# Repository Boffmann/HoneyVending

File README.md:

# Honey Vending
`Honey Vending` is a vending machine for honey I am building. This repository contains all assets regarding software and hardware.

## Components
The honey vending machine consists of multiple components and a software program.

* Customers can insert money via a programmable coin acceptor like [this one](https://www.sparkfun.com/products/11636).
* The currently insterted amount is shown via a [TM1637 Display Module](https://www.amazon.com/DEVMO-Digital-Display-Module-Arduino/dp/B07R64BC38/ref=sr_1_1_sspa?keywords=tm1637&qid=1644671514&sr=8-1-spons&psc=1&spLa=ZW5jcnlwdGVkUXVhbGlmaWVyPUExVEc0TVhXVzVPQVNMJmVuY3J5cHRlZElkPUEwMDExODY5MjVIRVJISzI5SlFRTCZlbmNyeXB0ZWRBZElkPUEwMTgzMTM3M0JCWDJUNTJPTUNSJndpZGdldE5hbWU9c3BfYXRmJmFjdGlvbj1jbGlja1JlZGlyZWN0JmRvTm90TG9nQ2xpY2s9dHJ1ZQ==).
* All products are behind individually addressable doors that are controled by 12V electromagnetic locks like [this](https://www.amazon.com/uxcell-Electromagnetic-Solenoid-Assembly-Electirc/dp/B07TMWY94C/ref=sr_1_6?keywords=12v+door+lock&qid=1644671675&sr=8-6).
* Each door is linked to a button on a customly designed button rack.

The entire machine is managed by a ESP32 microcontroller that runs a custom program and links all parts.

## Structure
The project is structured as follows:

* **CADs**: Contains CAD files for all individual components and PCBs that are featured in this project
* **src**: The source files for the software programm controling the vending machines workflow

## Deploy
TODO

## Run tests
The unittests feature an independent build workflow using CMake. They cover all code that does not directly interact with the ESP hardware.

To compile and run unittests make sure to have `CMake` installed and perform following commands:

```
mkdir build && cd build
cmake ..
make
./unittest
```

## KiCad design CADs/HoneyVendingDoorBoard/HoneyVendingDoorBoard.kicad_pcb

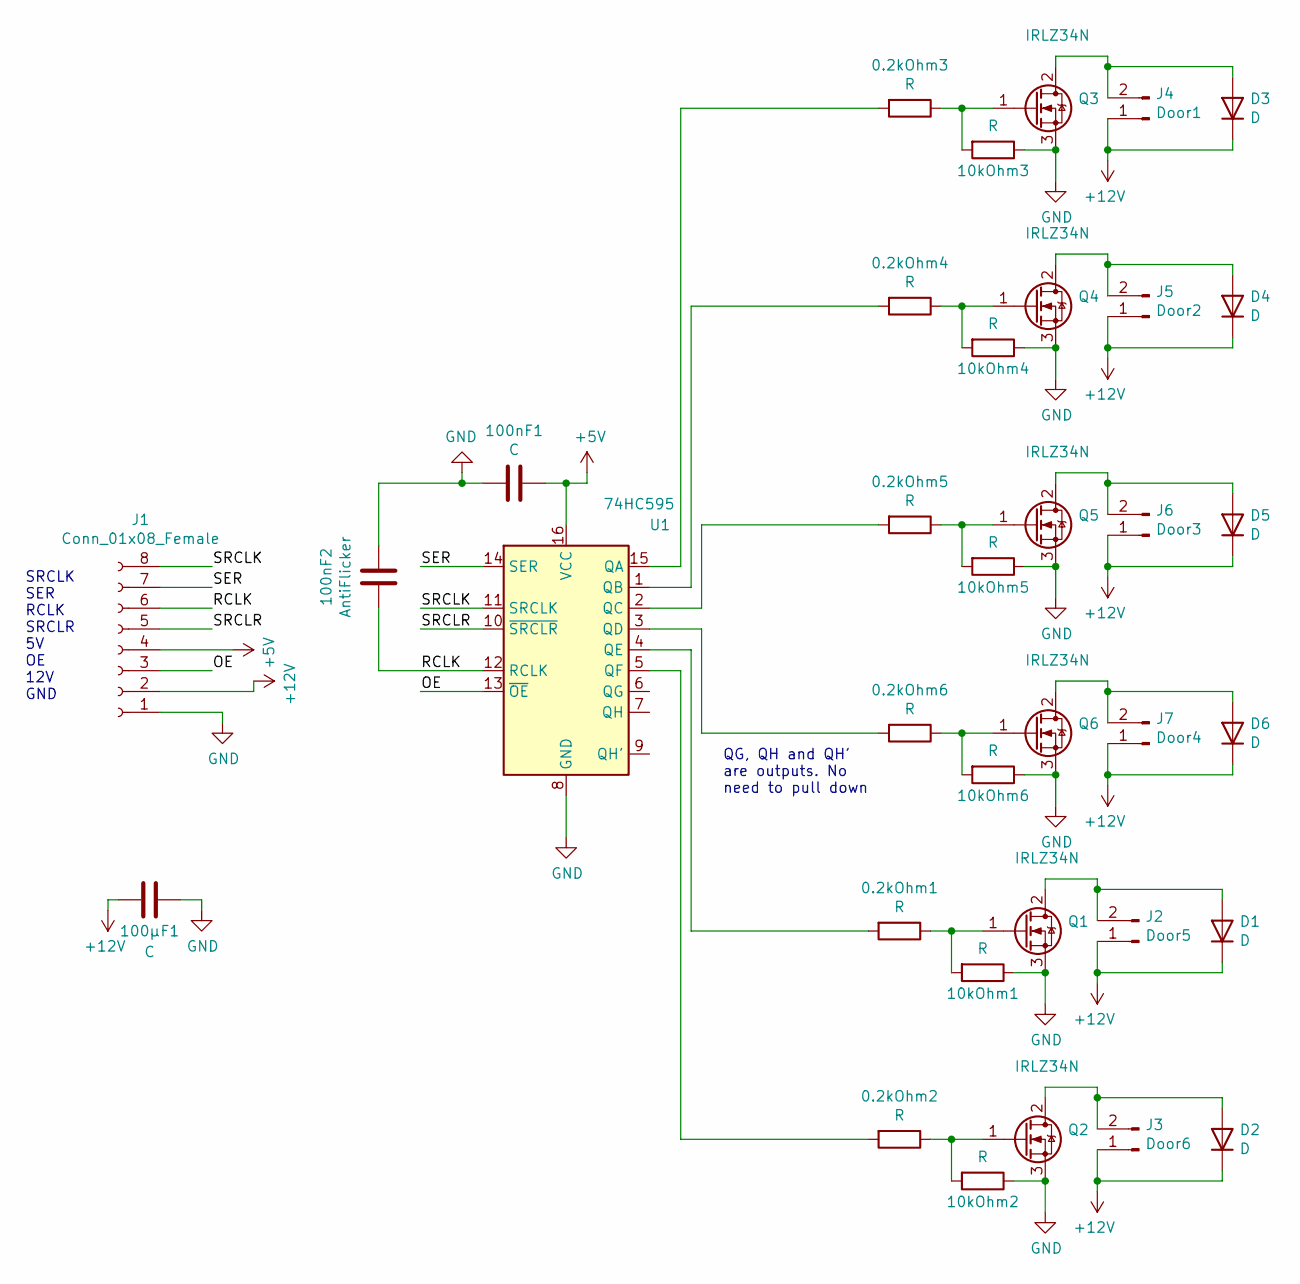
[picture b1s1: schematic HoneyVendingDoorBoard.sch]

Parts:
0.2kOhm1, 0.2kOhm2, 0.2kOhm3, 0.2kOhm4, 0.2kOhm5, 0.2kOhm6, 10kOhm1, 10kOhm2, 10kOhm3, 10kOhm4, 10kOhm5, 10kOhm6: R; R_0805_2012Metric_Pad1.15x1.40mm_HandSolder
100nF1: C; C_Disc_D6.0mm_W2.5mm_P5.00mm
100nF2: AntiFlicker; C_Disc_D6.0mm_W2.5mm_P5.00mm
100µF1: C; CP_Radial_D8.0mm_P3.50mm
D1, D2, D3, D4, D5, D6: D; D_DO-41_SOD81_P5.08mm_Vertical_AnodeUp
J1: Conn_01x08_Female; PinHeader_2x04_P2.54mm_Vertical
J2: Door5; PinHeader_1x02_P2.54mm_Vertical
J3: Door6; PinHeader_1x02_P2.54mm_Vertical
J4: Door1; PinHeader_1x02_P2.54mm_Vertical
J5: Door2; PinHeader_1x02_P2.54mm_Vertical
J6: Door3; PinHeader_1x02_P2.54mm_Vertical
J7: Door4; PinHeader_1x02_P2.54mm_Vertical
Q1, Q2, Q3, Q4, Q5, Q6: IRLZ34N; TO-220-3_Vertical
U1: 74HC595

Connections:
+5V: 100nF1.1, J1.4, U1.16 (VCC)
+12V: 100µF1.1, D1.1 (K), D2.1 (K), D3.1 (K), D4.1 (K), D5.1 (K), D6.1 (K), J1.2, J2.1, J3.1, J4.1, J5.1, J6.1, J7.1; also elsewhere on the board
/OE: J1.3, U1.13 (~OE)
/RCLK: 100nF2.2, J1.6, U1.12 (RCLK)
/SER: J1.7, U1.14 (SER)
/SRCLK: J1.8, U1.11 (SRCLK)
/SRCLR: J1.5, U1.10 (~SRCLR)
GND: 10kOhm1.1, 10kOhm2.1, 10kOhm3.1, 10kOhm4.1, 10kOhm5.1, 10kOhm6.1, 100nF1.2, 100nF2.1, 100µF1.2, J1.1, Q1.3 (S), Q2.3 (S), Q3.3 (S), Q4.3 (S), Q5.3 (S), Q6.3 (S), U1.8 (GND); also elsewhere on the board
unnamed: 0.2kOhm1.1, 10kOhm1.2, Q1.1 (G)
unnamed: 0.2kOhm1.2, U1.4 (QE)
unnamed: 0.2kOhm2.1, 10kOhm2.2, Q2.1 (G)
unnamed: 0.2kOhm2.2, U1.5 (QF)
unnamed: 0.2kOhm3.1, 10kOhm3.2, Q3.1 (G)
unnamed: 0.2kOhm3.2, U1.15 (QA)
unnamed: 0.2kOhm4.1, 10kOhm4.2, Q4.1 (G)
unnamed: 0.2kOhm4.2, U1.1 (QB)
unnamed: 0.2kOhm5.1, 10kOhm5.2, Q5.1 (G)
unnamed: 0.2kOhm5.2, U1.2 (QC)
unnamed: 0.2kOhm6.1, 10kOhm6.2, Q6.1 (G)
unnamed: 0.2kOhm6.2, U1.3 (QD)
unnamed: D1.2 (A), J2.2, Q1.2 (D)
unnamed: D2.2 (A), J3.2, Q2.2 (D)
unnamed: D3.2 (A), J4.2, Q3.2 (D)
unnamed: D4.2 (A), J5.2, Q4.2 (D)
unnamed: D5.2 (A), J6.2, Q5.2 (D)
unnamed: D6.2 (A), J7.2, Q6.2 (D)

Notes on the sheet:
SRCLK SER RCLK SRCLR 5V OE 12V GND
QG, QH and QH' are outputs. No need to pull down

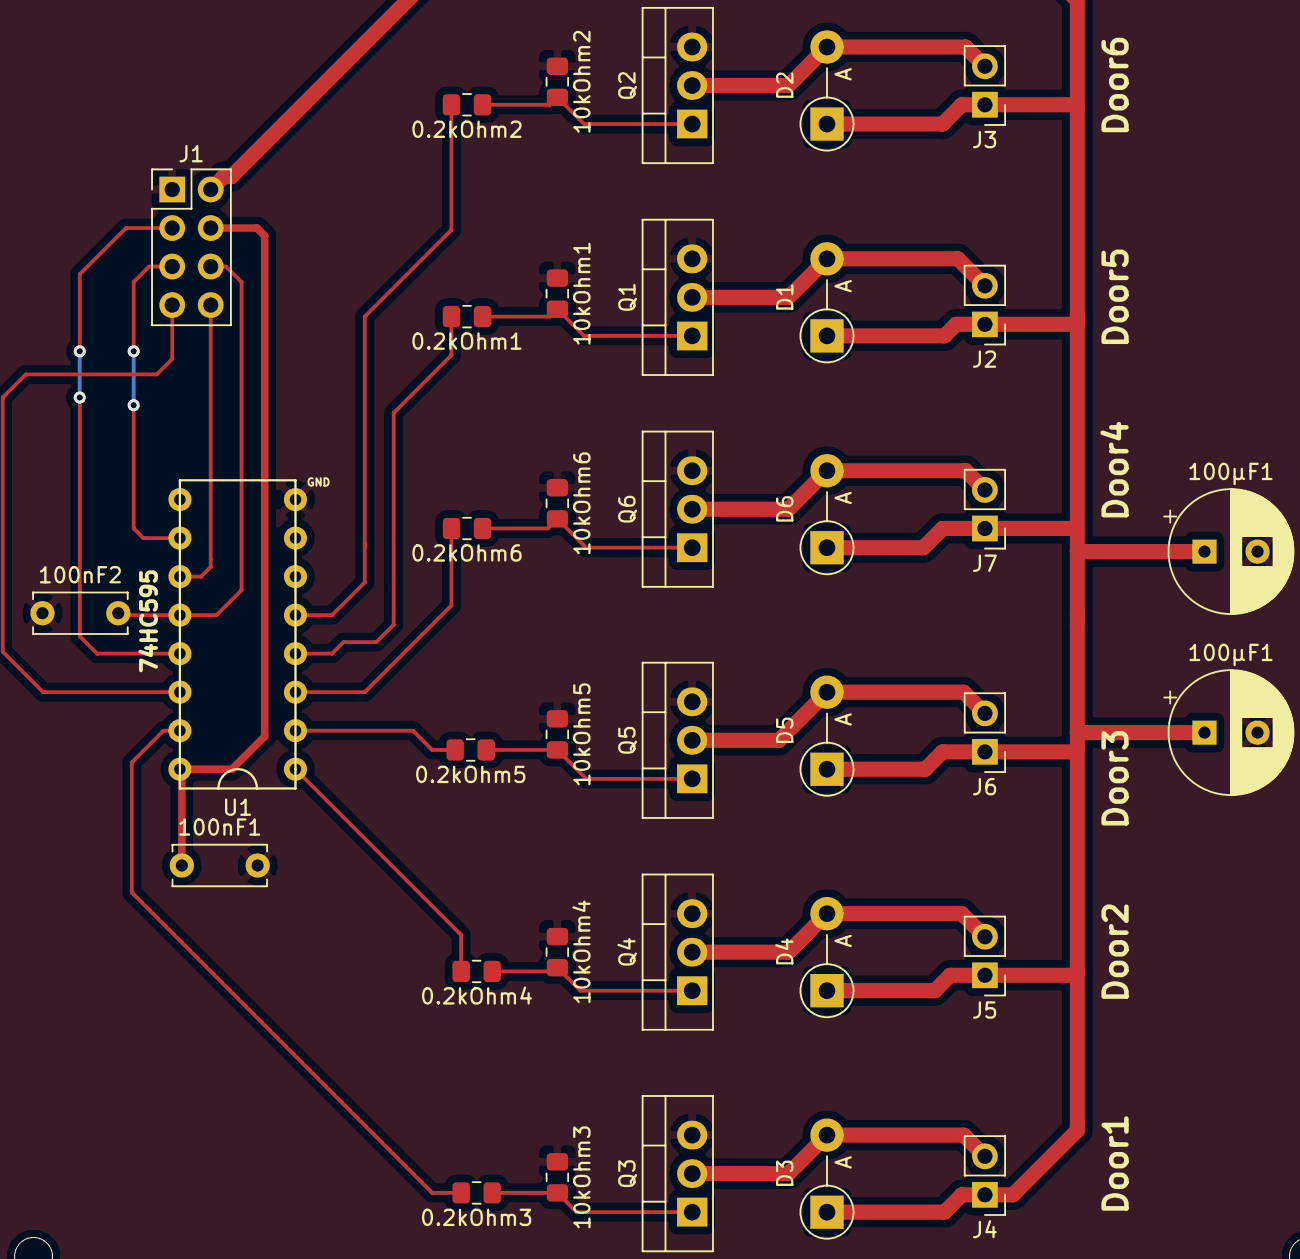
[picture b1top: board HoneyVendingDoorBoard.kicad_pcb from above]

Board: 2 copper layers, 36 parts (0 on the bottom side), 26 nets.

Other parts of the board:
100µF1#2: C; CP_Radial_D8.0mm_P3.50mm

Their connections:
+12V: 100µF1#2.1; also elsewhere on the board
GND: 100µF1#2.2; also elsewhere on the board

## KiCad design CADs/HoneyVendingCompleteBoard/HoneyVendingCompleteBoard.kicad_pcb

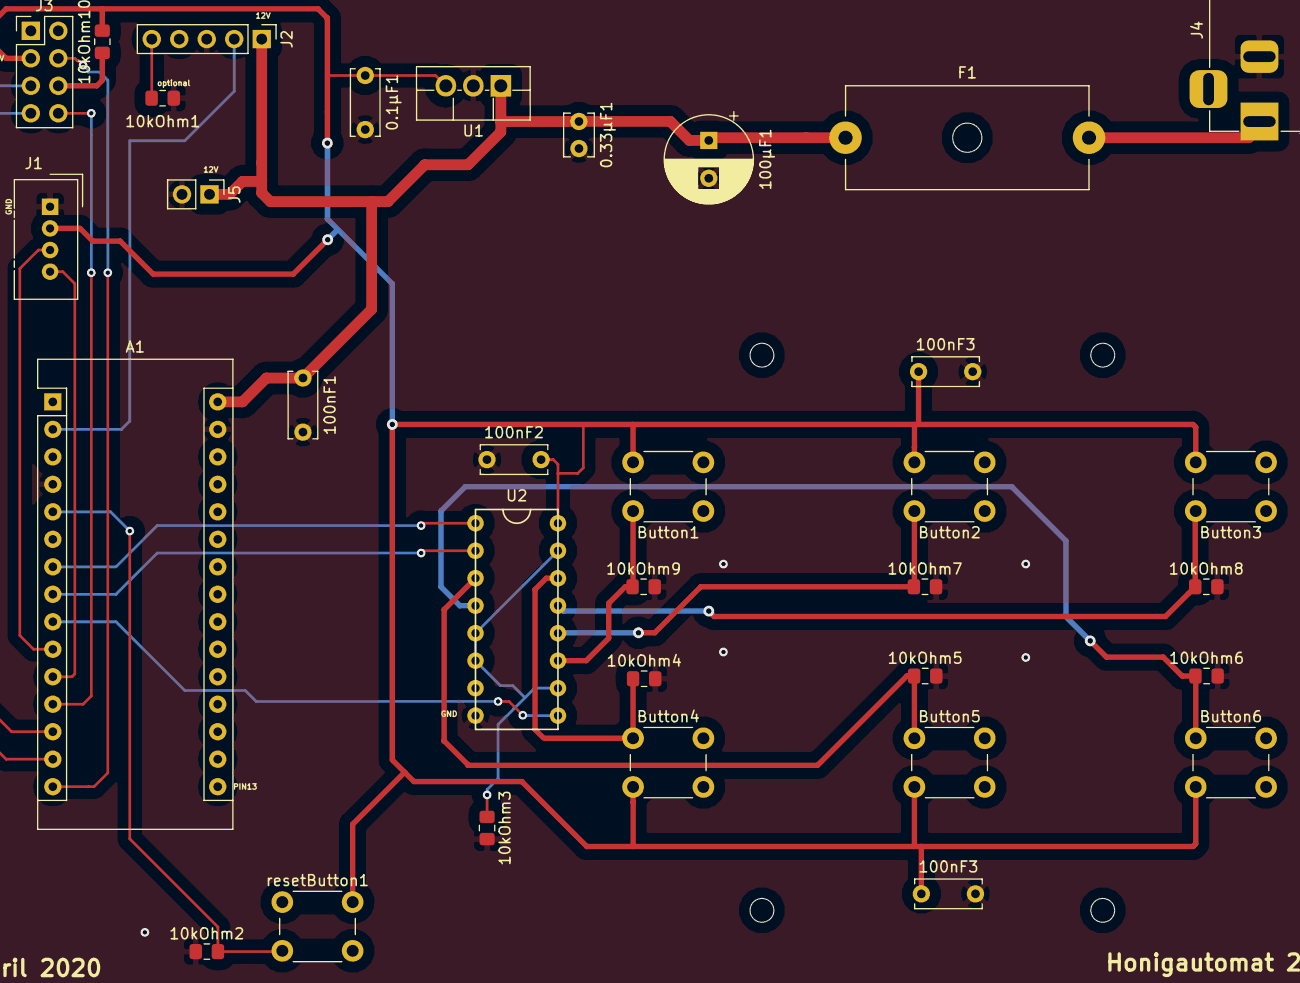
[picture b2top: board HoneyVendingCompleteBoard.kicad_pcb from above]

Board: 2 copper layers, 33 parts (0 on the bottom side), 24 nets.

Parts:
0.1µF1: VR3; C_Disc_D6.0mm_W2.5mm_P5.00mm
0.33µF1: VR2; C_Disc_D3.8mm_W2.6mm_P2.50mm
10kOhm1: CoinInhibitPullDown; R_0805_2012Metric_Pad1.15x1.40mm_HandSolder
10kOhm2: ResetPD; R_0805_2012Metric_Pad1.15x1.40mm_HandSolder
10kOhm3: R; R_0805_2012Metric_Pad1.15x1.40mm_HandSolder
10kOhm4: ButtonR4; R_0805_2012Metric_Pad1.15x1.40mm_HandSolder
10kOhm5: ButtonR5; R_0805_2012Metric_Pad1.15x1.40mm_HandSolder
10kOhm6: ButtonR6; R_0805_2012Metric_Pad1.15x1.40mm_HandSolder
10kOhm7: ButtonR2; R_0805_2012Metric_Pad1.15x1.40mm_HandSolder
10kOhm8: ButtonR3; R_0805_2012Metric_Pad1.15x1.40mm_HandSolder
10kOhm9: ButtonR1; R_0805_2012Metric_Pad1.15x1.40mm_HandSolder
10kOhm10: DoorClearPullUp; R_0805_2012Metric_Pad1.15x1.40mm_HandSolder
100nF1: ArduinoDecouple; C_Disc_D6.0mm_W2.5mm_P5.00mm
100nF2: ButtonDecouple; C_Disc_D6.0mm_W2.5mm_P5.00mm
100nF3, 100nF3#2: ButtonC; C_Disc_D6.0mm_W2.5mm_P5.00mm
100µF1: VR1; CP_Radial_D8.0mm_P3.50mm
A1: Arduino_Nano_v3.x; Arduino_Nano
Button1, Button2, Button3, Button4, Button5, Button6: SW_DPST_x2; SW_PUSH_6mm_H9.5mm
F1: Fuse; Fuseholder_Cylinder-5x20mm_Schurter_0031_8201_Horizontal_Op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
J1: SegmentPins; NS-Tech_Grove_1x04_P2mm_Vertical
J2: CoinPins; PinHeader_1x05_P2.54mm_Vertical
J3: ConnToDoors; PinHeader_2x04_P2.54mm_Vertical
J4: 12V Power; BarrelJack_Horizontal
J5: Power Line; PinHeader_1x02_P2.54mm_Vertical
U1: L7805; TO-220F-3_Vertical
U2: 74HC165
resetButton1: SW_DPST_x2; SW_PUSH_6mm_H9.5mm

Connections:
+5V: 0.1µF1.1, 10kOhm10.2, 100nF2.2, 100nF3.1, 100nF3#2.1, Button1.2, Button2.2, Button3.2, Button4.2, Button5.2, Button6.2, J1.2, J3.3, U1.3, U2.16, resetButton1.1
+12V: F1.2, J4.1
/12VFused: 0.33µF1.1, 100nF1.1, 100µF1.1, A1.30, F1.1, J2.1, J5.1, U1.1
/CoinSerial: A1.2, J2.2
/PISOClock: A1.8, U2.2
/PISOOutput: A1.9, U2.9
/PISO_SL: A1.7, U2.1
/doorOE: A1.15, J3.4
/doorRCLK: A1.13, J3.5
/doorSER: A1.12, J3.8
/doorSRCLK: A1.14, J3.7
/segmentClock: A1.11, J1.4
/segmentSignal: A1.10, J1.3
GND: 0.1µF1.2, 0.33µF1.2, 10kOhm1.1, 10kOhm2.1, 10kOhm3.2, 10kOhm4.2, 10kOhm5.2, 10kOhm6.2, 10kOhm7.2, 10kOhm8.2, 10kOhm9.2, 100nF1.2, 100nF2.1, 100nF3.2, 100nF3#2.2, 100µF1.2, A1.4, A1.29, J1.1, J2.3, J4.2, J5.2, U1.2, U2.8
unnamed: 10kOhm1.2, J2.5
unnamed: 10kOhm2.2, A1.5, resetButton1.2
unnamed: 10kOhm3.1, U2.5, U2.6, U2.10, U2.15
unnamed: 10kOhm4.1, Button4.1, U2.14
unnamed: 10kOhm5.1, Button5.1, U2.3
unnamed: 10kOhm6.1, Button6.1, U2.4
unnamed: 10kOhm7.1, Button2.1, U2.12
unnamed: 10kOhm8.1, Button3.1, U2.13
unnamed: 10kOhm9.1, Button1.1, U2.11
unnamed: 10kOhm10.1, J3.6

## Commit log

2018-06-09 platformio init
2018-06-09 Set board to uno
2018-06-09 Implements basic coin acceptor code to detect inserted coin
2018-07-17 Adds some comments
2018-07-17 Sets vim .swp files to gitignore
2018-07-17 Adds method to shift out bit to open/close door
2018-07-17 Adds servo instance and method to rotate servo
2018-07-17 Adds method to register pressed button
2018-07-17 Created LICENSE file
2018-07-17 Changes Door enum to array mapping the shift out values
2018-07-18 Adds config header for all numbers and configurations
2018-07-18 Adds shiftIn in new Utils file to read serial input from shift register
2018-07-18 Deletes dependency to own implementation of shiftIn by using shiftIn from Arduino
2018-07-20 Adds method to count digits of a number and adds seven segment display support
2018-07-20 Reworks display method; Adds some new state
2018-07-20 Separates output pin for doors and display
2018-08-26 Adds dependency for 7 segment display directly to project
2018-09-30 Reworked getButtonPressed(). Methods now works, but pins act weird
2020-03-30 Adds SIPO, PISO and CoinSerial class. Remove old srcs from git
2020-03-30 Adds KiCad files
2020-03-30 Interrupt routines
2020-03-30 Update mainboard schematic
2020-03-30 Add include dir
2020-03-30 Add display and shelf class
2020-03-31 Add Serial Wrapper
2020-03-31 Feature complete and compiles
2020-03-31 Add comments and delete PISO and SIPO
2020-03-31 Use void for functions with no params
2020-04-05 Adds schematic pdfs
2020-04-05 Create honeyLib and add first test
2020-04-05 Shelf and Display working
2020-04-06 Buttons work
2020-04-06 Bugfix in display and coinSerial works
2020-04-06 CoinSerial update method returns bool
2020-04-06 Adds buttonrack
2020-04-06 Adds test for 74HC165
2020-04-07 Reworded PCBs and added PCB pdfs
2020-04-08 Updates boards
2020-04-08 Applying nicos feedback for boards
2020-04-09 Split Main Board into Main Board and Button Board
2022-02-08 Complete restructure codewise
2022-02-14 Separate code into libs
